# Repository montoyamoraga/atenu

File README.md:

# atenu

## About

atenu is an open source hardware Eurorack dual passive attenuator module by [piruetas](https://piruetas.xyz), part of popusintes. It has two independent channels, each with an input jack, a linear potentiometer and an output jack, and needs no power. The board is made in KiCad 10 with its own local footprint, 3D model and SPICE libraries, included in each revision's `bibliotecas/` folder, and the panel is made in OpenSCAD with the shared modules from [popusintes-cajas-paneles](https://github.com/piruetasxyz/popusintes-cajas-paneles), included as a git submodule in `terceros/`. Hardware is licensed under CERN-OHL-P-2.0, and the panel and documentation under CC-BY-SA-4.0 (see [LICENSE.md](./LICENSE.md)). Documentation, schematic, board render and bill of materials (in Spanish): <https://piruetas.xyz/atenu/>.

## Acerca de

Atenuador pasivo doble eurorack de [piruetas](https://piruetas.xyz), parte de popusintes, hecho en KiCad y publicado como hardware de código abierto.

Documentación, esquemático, placa y Bill of materials: <https://piruetas.xyz/atenu/>.

## Características

- 2 canales independientes, cada uno con entrada, potenciómetro y salida.
- Potenciómetros lineales B100k de 9 mm (Alpha RD901F, de [Thonk](https://www.thonk.co.uk/)), cableados como divisor de voltaje: entrada en un extremo, GND en el otro, salida en el cursor.
- Jacks mono de 3.5 mm QingPu WQP-PJ398SM (tipo Thonkiconn). Las entradas tienen el switch a GND: sin cable enchufado, la salida queda en 0 V.
- Pasivo: no lleva header de alimentación ni consume corriente. Solo atenúa (ganancia entre 0 y 1), no amplifica ni invierte.
- Placa de 25 × 90 mm, 2 capas, solo componentes THT. Panel de 5 HP.

## Manual de uso

El manual de uso está en la [documentación](https://piruetas.xyz/atenu/#manual-de-uso).

## Revisiones

- `v0.1 rev-a`: diseñada en octubre 2026 y fabricada en JLCPCB. Funciona, pero los potenciómetros quedaron al revés (ver errores abajo).
- `v0.1 rev-b`: en desarrollo. Corrige la huella de los potenciómetros y agrega simulación SPICE.

### Errores conocidos de rev-a

El esquemático está bien; el error está en la huella.

- **Potenciómetros al revés.** La huella `POT_TH_Alps_RK09K_Single_Vertical` calza mecánicamente con los potenciómetros Alpha RD901F, pero tiene los pads 1 y 3 intercambiados respecto a sus patas. Girando en sentido horario el cursor va hacia GND (silencio), y en antihorario hacia la entrada (volumen máximo).

Como los potenciómetros son lineales (B100k), la curva es la misma en ambos sentidos: solo cambia la dirección. No hay arreglo limpio para las placas ya fabricadas: funcionan al revés (antihorario = más volumen). Es el mismo error de suma rev-a.

### Simulación

rev-b se puede simular en KiCad (Inspeccionar → Simulador → Ejecutar). Los modelos de los conectores están en [bibliotecas/spice/eurorack.lib](./hardware/atenu-v-0-rev-b/bibliotecas/spice/eurorack.lib), adaptados de suma, para no agregar fuentes al esquemático: J1 y J3 se comportan como osciladores senoidales de 10 Vpp (J1 a 220 Hz, J3 a 330 Hz; se cambian con `amplitud` y `frecuencia` en Sim.Params), y J2 y J4 como la entrada de 100k de otro módulo. La posición de cada potenciómetro se cambia con `pos` en Sim.Params (0 = antihorario completo, 1 = horario completo).

Con RV1 en `pos=0.75` y RV2 en `pos=0.25`, ngspice da 3.16 V y 1.05 V de pico en las salidas, para 5 V de pico en las entradas (ganancia 0.63 y 0.21; la carga de 100k baja un poco la ganancia respecto a la posición del potenciómetro).

### Pendientes para rev-b

Ya está hecho en [hardware/atenu-v-0-rev-b](./hardware/atenu-v-0-rev-b):

- Biblioteca propia `popusintes` ([bibliotecas/popusintes.pretty](./hardware/atenu-v-0-rev-b/bibliotecas/popusintes.pretty) y [bibliotecas/popusintes.3dshapes](./hardware/atenu-v-0-rev-b/bibliotecas/popusintes.3dshapes)), copiada de [popusintes-esquematicos-placas](https://github.com/piruetasxyz/popusintes-esquematicos-placas) para que el repositorio sea autocontenido, con la huella corregida `Potenciometro_Alpha_RD901F_Vertical`: misma geometría que la de rev-a, con los pads 1 y 3 intercambiados. Visto de frente con las patas hacia abajo, pad 1 = pata izquierda (antihorario, GND), pad 3 = pata derecha (horario, entrada).
- Pistas de entrada de RV1 y RV2 movidas a la pata derecha. DRC sin conexiones pendientes y sin diferencias con el esquemático.
- Todo renombrado de rev-a a rev-b, incluida la carpeta de salida de los gerbers (`../atenu-v-0-rev-b-fab/`), para no pisar los archivos de rev-a. La fecha de la serigrafía quedó en `2026-11`.
- Modelos SPICE y campos `Sim.*` en el esquemático y en la placa.

Falta:

- [ ] Rellenar las zonas en KiCad (tecla B), guardar y revisar los potenciómetros en el visor 3D. **Antes de generar gerbers**: el relleno guardado de la zona GND es anterior al cambio de pads, así que todavía cubre la pata nueva de la entrada (la dejaría en corto con GND) y no llega a la pata nueva de GND. El DRC sin rellenar muestra esos errores; después de rellenar, el DRC queda sin conexiones pendientes y sin diferencias con el esquemático.
- [ ] Revisar el texto de la serigrafía en un computador con las fuentes del proyecto instaladas antes de generar los gerbers.
- [ ] Generar gerbers y archivos de taladrado de rev-b (`hardware/atenu-v-0-rev-b-fab`).
- [ ] Panel de rev-b: las posiciones de los potenciómetros y jacks no cambiaron, así que el panel de rev-a calza. Falta decidir si se copia a `panel/atenu-v-0-rev-b` con `VERSION = "v0.1 rev-b"`.
- [ ] Actualizar [kicad-retrata.yml](./kicad-retrata.yml) y [docs](./docs) para que apunten a rev-b.

## Estructura del repositorio

- [hardware/atenu-v-0-rev-a](./hardware/atenu-v-0-rev-a): proyecto de KiCad (esquemático y placa), los archivos fuente del diseño.
- [hardware/atenu-v-0-rev-a/bibliotecas](./hardware/atenu-v-0-rev-a/bibliotecas): huellas y modelos 3D usados por el proyecto. Van en el repositorio para que el proyecto de KiCad se abra sin instalar bibliotecas adicionales.
- [hardware/atenu-v-0-rev-a-fab](./hardware/atenu-v-0-rev-a-fab): gerbers y archivos de taladrado para fabricar la placa.
- [hardware/atenu-v-0-rev-b](./hardware/atenu-v-0-rev-b): proyecto de KiCad de rev-b (en desarrollo). Sus [bibliotecas](./hardware/atenu-v-0-rev-b/bibliotecas) incluyen la biblioteca propia `popusintes` con la huella corregida del potenciómetro, y los modelos SPICE en `spice/`.
- [panel/atenu-v-0-rev-a](./panel/atenu-v-0-rev-a): archivos fuente de OpenSCAD del panel de 5 HP, con los agujeros de los potenciómetros y jacks de la placa rev-a. Se abre [atenu.scad](./panel/atenu-v-0-rev-a/atenu.scad); la versión grabada en el panel está en [versiones.scad](./panel/atenu-v-0-rev-a/versiones.scad).
- [terceros/popusintes-cajas-paneles](https://github.com/piruetasxyz/popusintes-cajas-paneles): submódulo de git con las constantes eurorack y las funciones y módulos de OpenSCAD compartidos entre las cajas y paneles de popusintes. Para clonar el repositorio con el submódulo: `git clone --recursive https://github.com/piruetasxyz/atenu.git`, o `git submodule update --init` si ya estaba clonado.
- [docs](./docs): documentación, publicada en <https://piruetas.xyz/atenu/>. Las capturas del esquemático y de la placa, y la tabla de Bill of materials, las genera [kicad-retrata](https://github.com/piruetasxyz/kicad-retrata) en cada push (ver [kicad-retrata.yml](./kicad-retrata.yml)).
- [LICENSES](./LICENSES): textos completos de las licencias.

## Fabricación

Como es hardware de código abierto, los archivos fuente de KiCad, los archivos de fabricación de [hardware/atenu-v-0-rev-a-fab](./hardware/atenu-v-0-rev-a-fab) y la [Bill of materials](https://piruetas.xyz/atenu/#bill-of-materials-v01-rev-a) están publicados para que cualquiera pueda estudiar, modificar y fabricar el diseño. piruetas no da soporte para unidades fabricadas o armadas por terceros.

## Créditos

- Aarón Montoya-Moraga: investigación, esquemático, PCB, panel, fabricación y documentación.

## Licencia

atenu es (c) 2026 piruetas SpA / Aarón Montoya-Moraga.

- Hardware (`hardware/`): [CERN-OHL-P-2.0](./LICENSES/CERN-OHL-P-2.0.txt).
- Panel (`panel/`): [CC-BY-SA-4.0](./LICENSES/CC-BY-SA-4.0.txt).
- Documentación (`docs/`): [CC-BY-SA-4.0](./LICENSES/CC-BY-SA-4.0.txt).
- Biblioteca compartida (`terceros/popusintes-cajas-paneles`): submódulo con su propia licencia, MIT.
- El nombre, logo y marca de piruetas no están cubiertos por estas licencias: ver [LicenseRef-piruetas-branding](./LICENSES/LicenseRef-piruetas-branding.txt).

Ver [LICENSE.md](./LICENSE.md) para los detalles. El repositorio sigue la especificación [REUSE](https://reuse.software/).

### Pendiente antes de certificar con OSHWA

atenu todavía no está postulado a la certificación de [OSHWA](https://certification.oshwa.org/). Antes de postular hay que corregir las licencias de algunos archivos de terceros en las `bibliotecas/` de cada revisión: hoy [REUSE.toml](./REUSE.toml) los marca como CERN-OHL-P-2.0 de piruetas junto con todo `hardware/**`, pero no son trabajo propio.

| Archivo | Origen | Licencia | Cómo se verificó |
| --- | --- | --- | --- |
| `PJ398SM.step` (modelo 3D del jack) | [clacktronics/AudioJacks](https://github.com/clacktronics/AudioJacks), "Copyright (c) 2021 Barwise" | MIT | archivo idéntico (mismo hash) |
| `Jack_3.5mm_QingPu_WQP-PJ398SM_Vertical.kicad_mod` (huella del jack) | [clacktronics/AudioJacks](https://github.com/clacktronics/AudioJacks), convertida al formato nuevo de KiCad | MIT | mismo nombre, descripción y etiquetas |
| `ALPHA-RD901F-40.step` (modelo 3D del potenciómetro) | [dhaillant/kicad-3dmodels](https://github.com/dhaillant/kicad-3dmodels), commit `e87a021` (2018-09-09) | GPL-3.0 | archivo idéntico (mismo hash); la licencia del repositorio es anterior a ese commit |
| Huella del potenciómetro (`POT_TH_Alps_RK09K_Single_Vertical` en rev-a, `Potenciometro_Alpha_RD901F_Vertical` en rev-b) | muy probablemente la biblioteca de huellas de KiCad, rotada; en rev-b además con los pads 1 y 3 intercambiados | CC-BY-SA-4.0 con la excepción de KiCad para diseños | descripción igual a la de la biblioteca antigua de KiCad y misma geometría; probable, no confirmado |
| `SOD-123FL_L2.8-W1.8-LS3.7-R-RD.step` / `.wrl` y `Diodo_SOD-123FL.kicad_mod` (solo en rev-b) | EasyEDA/LCSC, convertidos con `easyeda2kicad` | sin licencia clara | atenu no los usa: vienen en la copia completa de `popusintes` |

Los dos modelos 3D llegaron a través de la biblioteca BYOM de [popusintes-esquematicos-placas](https://github.com/piruetasxyz/popusintes-esquematicos-placas), que no trae archivo de licencia ni indica de dónde salieron sus archivos.

Falta:

- [ ] Decidir el modelo 3D del potenciómetro: mantener el de dhaillant (GPL-3.0) y agregar su fuente de FreeCAD, `ALPHA-RD901F-40.fcstd` del mismo commit, como pide la GPL; o reemplazarlo por el modelo 3D `Potentiometer_Alps_RK09K_Single_Vertical` de la biblioteca de KiCad, que es casi igual y tiene la licencia de la biblioteca de KiCad. Como el modelo es un archivo aparte que solo se usa para el render 3D, no debería afectar la licencia CERN-OHL-P-2.0 de la placa (lectura propia, no es asesoría legal).
- [ ] Agregar a [LICENSES](./LICENSES) los textos que falten: `MIT.txt`, `GPL-3.0-only.txt` (si se mantiene el modelo de dhaillant) y una `LicenseRef` con la excepción de la biblioteca de KiCad.
- [ ] Agregar en [REUSE.toml](./REUSE.toml) una anotación por cada archivo de terceros, después de la de `hardware/**` para que la reemplace, en rev-a y en rev-b.
- [ ] Quitar de rev-b los archivos del diodo SOD-123FL, que atenu no usa y no tienen licencia clara.
- [ ] Agregar una sección de modelos y huellas de terceros a este README y a [LICENSE.md](./LICENSE.md), con créditos a clacktronics/Barwise, dhaillant y la biblioteca de KiCad.
- [ ] Hacer los mismos arreglos en [popusintes-esquematicos-placas](https://github.com/piruetasxyz/popusintes-esquematicos-placas), que es la fuente de la biblioteca `popusintes`, y en suma, que tiene los mismos archivos.
- [ ] Correr `reuse lint` (está en [requirements.txt](./requirements.txt)) y revisar que no queden archivos sin licencia.

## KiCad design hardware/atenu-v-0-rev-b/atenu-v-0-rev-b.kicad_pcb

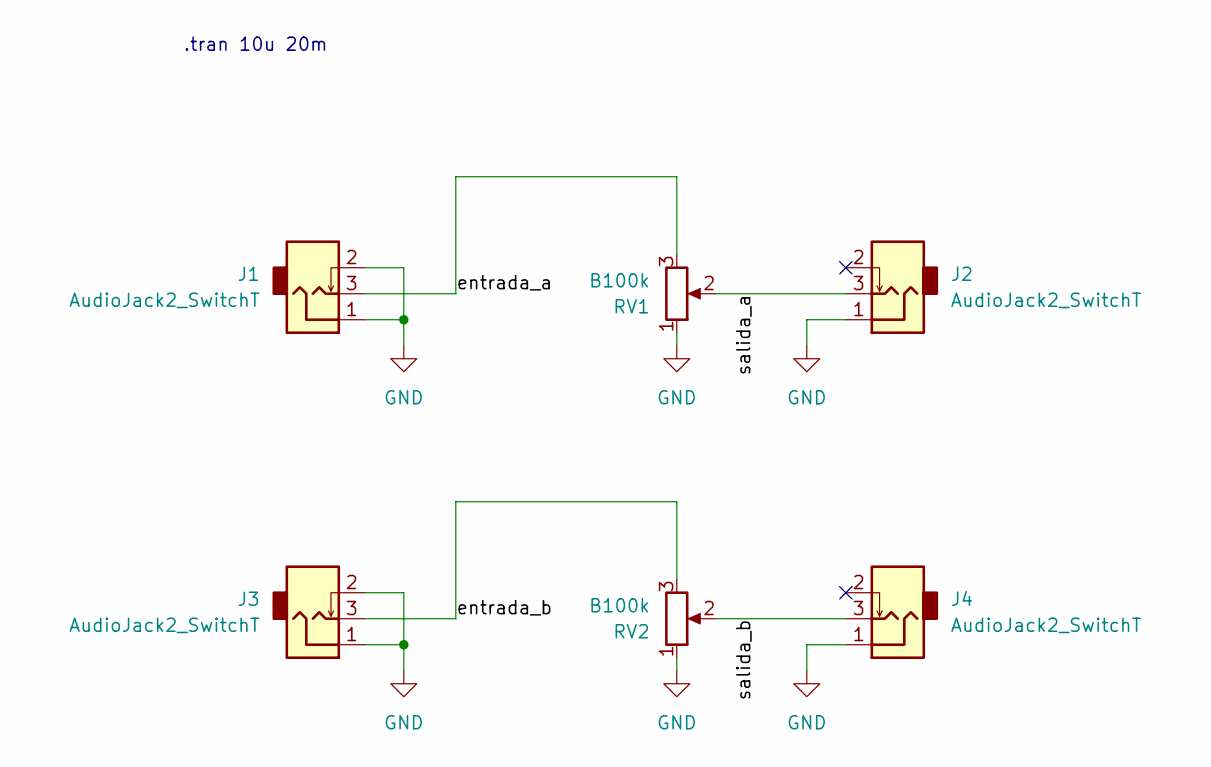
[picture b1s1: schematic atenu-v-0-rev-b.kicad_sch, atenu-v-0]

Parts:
J1, J2, J3, J4: AudioJack2_SwitchT; Jack_3.5mm_QingPu_WQP-PJ398SM_Vertical
RV1, RV2: B100k; Potenciometro_Alpha_RD901F_Vertical

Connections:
/entrada_a: J1.3, RV1.3
/entrada_b: J3.3, RV2.3
/salida_a: J2.3, RV1.2
/salida_b: J4.3, RV2.2
GND: J1.1, J1.2, J2.1, J3.1, J3.2, J4.1, RV1.1, RV2.1

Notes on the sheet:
.tran 10u 20m

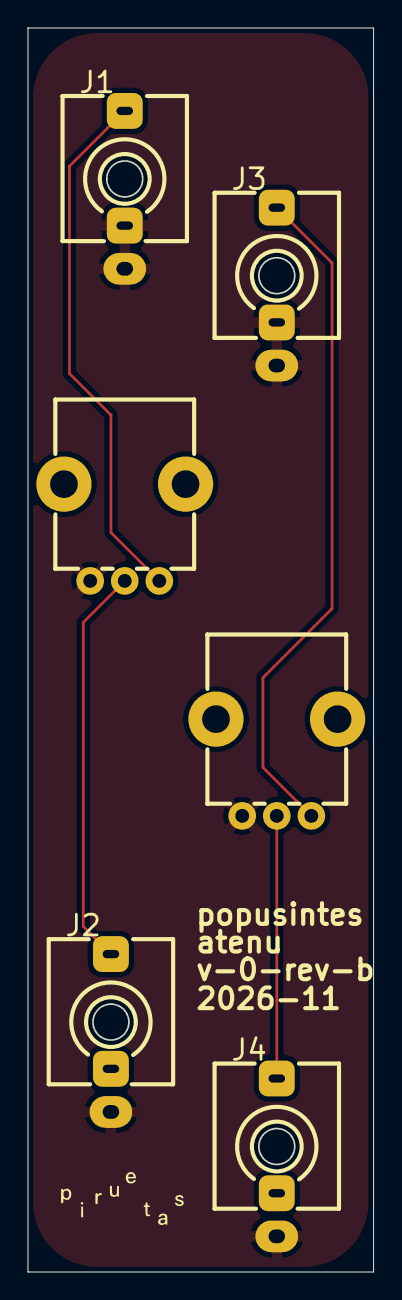
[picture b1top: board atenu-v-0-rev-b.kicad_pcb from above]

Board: 2 copper layers, 25.0 x 90.0 mm, 6 parts (0 on the bottom side), 5 nets.
